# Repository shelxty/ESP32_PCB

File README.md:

# ESP32-C3 USB-C Devboard 

This is a custom 4-layer ESP32-C3 devboard built from scratch in KiCad, built around the ESP32-C3-WROOM-02. It's my second devboard (if a regulator can be counted as a devboard) with a full breakout of GPIOs and reset/boot buttons.

## Motivation 
This is my second-ever PCB; I built it to follow up on my first project. I've been interested in how ESP32s work so I thought this would be the best way to explore it! This would be an actual useful, purposeful tool that I'd be able to use in built projects as well. It also pushed me to learn new skills, like ESD protection and multi-layer board design (well, multi-layer as in 4 instead of 2). 

## How the Components Work 

| **Designator** | **Part** | **Purpose** | 
|----------------|----------|-------------|
| U3 | ESP32-C3-WROOM-02 | The brain of the board basically (it's a RISC-V microcontroller module that has integrated WiFi & bluetooth, along with an antenna) | 
| J1 | 16-pin USB-C receptacle | Power entry (it takes in 5V) | 
| J2, J3 | 8-pin headers on the left & right side, respectively | Breaks out the GPIO pins | 
| U1 | USBLC6-2SC6 | Dual line ESD protection IC that suppresses voltage spikes before they reach the microcontroller | 
| D1 | PESD5V0L1ULD | A TVS diode that protects the voltage line (5V) from any ESD/transient voltage spikes that enter from the USB receptacle | 
| R3 | 0Ω resistor | Basically a routing jumper so that I don't have to remove a trace | 
| U2 | AP2112K-3.3 | Fixed 3.3V, 600mA LDO regulator (it basically takes the 5V input and regulates it into a stable 3.3V rail) | 
| C1, C2 | 4.7uF capacitors | These are input and output capacitors built around the regulator that smooths the 5V input and the regulated 3.3V output | 
| C3, C4, C5 | 4.7uF capacitors | Other decoupline capacitors except these around the module's power pins, so the supply is stable even during WiFi bursts | 
| C9, C10 | 100nF capacitors | These are high-frequency decoupling capacitors that are placed close to the regulator's pins (they filter out noise) | 
| R5 | 10kΩ resistor | This is a pull-up resistor that supports the enable (EN) line | 
| R7, R8 | 10kΩ resistor | These are two other pull-up resistors except they support different GPIO lines | 
| R1, R2 | 5.1kΩ resistor | Resistors on the RESET and BOOT button lines, respectively | 
| SW1 | "RESET" Push Button | Basically just... resets the chip... yeah. | 
| SW2 | "BOOT" Push Button | Pulls IO9 (the strapping pin that selects boot mode, as opposed to UART download mode) low when it's pressed | 
| R9 | 10kΩ resistor | This one is another pull-up resistor but it specifically works on the IO9 boot/strapping line (so the chip should boot normally if the BOOT button isn't being pressed | 
| Y1 | Crystal | An external crystal that provides a precise clock reference | 

**Hardware**
- Tool: KiCad 10
- Board: 4-layer PCB (F.Cu / In1.Cu / In2.Cu / B.Cu)
- Microcontroller: ESP32-C3-WROOM-02 RISC-V, WiFi + Bluetooth
- Regulator: AP2112K-3.3, 600mA LDO
- USB protection: USBLC6-2SC6 (data line ESD) + PESD5V0L1ULD (VBUS TVS diode)
- Power input: USB-C (5V)
- GPIOs: 16 pins broken out across two 8-pin 2.54mm headers (J2, J3)
- Controls: Reset button (SW1), Boot button (SW2)

## PCB Design 

_Schematic of the board -- I made sure to add comments & my own personal text for beginners like me_

_PCB design_

_A 3D view of the actual thing_

## Bill of Materials 
| **Item** |	**Description** |	**Reference** |	**Qty** |	**MOQ** |	**Value** |	**Per Unit Price ($)** |	**Total Price ($)** |	**Footprint** |	**MPN** |	**URL** | 
|------|--------------|-----------|-----|-----|-------|--------------------|------------------|-----------|-----|-----|
| 4u7 Capacitor |	Unpolarized capacitor |	C1,C2,C3,C4,C5 |	5 |	10 |	4u7 |	0.0505 |	0.51 |	Capacitor_SMD:C_0805_2012Metric |	CL21A475KBQNNNE |	[Link](https://www.lcsc.com/product-detail/C98192.html?s_z=s_c_Ceramic%2520Capacitors&spm=wm.fly.bg.0.xh&lcsc_vid=QQVaAVJeTlJdUVBVE1hcBVFWEwcNBVxeQwAPA1YHFQMxVlNeRVFeXl1XRlNeXzsOAxUeFF5JWBYZEEoKFBINSQcJGk4NBhADEA4cHktTRk8GEwkK) |
| 100n Capacitor |	Unpolarized capacitor |	C6,C9,C10 |	3 |	10 |	100n |	0.0192 |	0.19 |	Capacitor_SMD:C_0201_0603Metric |	0805B104K500CT |	[Link](https://www.lcsc.com/product-detail/C83055.html?s_z=s_c_Ceramic%2520Capacitors&spm=wm.fly.bg.3.xh&lcsc_vid=QQVaAVJeTlJdUVBVE1hcBVFWEwcNBVxeQwAPA1YHFQMxVlNeRVFeXl1XRlNeXzsOAxUeFF5JWBYZEEoKFBINSQcJGk4NBhADEA4cHktTRk8GEwkK) |
| Capacitor |	Unpolarized capacitor |	C7,C8,R4 |	3 |	100 |	0n |	0.0052 |	0.52 |	Capacitor_SMD:C_0201_0603Metric |	TCC0805X7R501K500DT |	[Link](https://www.lcsc.com/product-detail/C5375938.html?spm=wm.fly.bg.3.xh&lcsc_vid=QQVaAVJeTlJdUVBVE1hcBVFWEwcNBVxeQwAPA1YHFQMxVlNeRVFfV1ZVTlNXVzsOAxUeFF5JWBYZEEoKFBINSQcJGk4NBhADEA4cHktXRlVcSQwSGg0%3D) |
| ESD Diode |	Low capacitance unidirectional ESD protection diode, 5V, SOD-882D |	D1 |	1 |	5 |	PESD5V0L1ULD |	0.0978 |	0.49 |	Diode_SMD:D_SOD-882D |	PESD5V0L1ULD,315 |	[Link](https://www.lcsc.com/product-detail/C552557.html?s_z=s_p_PESD5V0L1ULD%252C315&spm=wm.fly.bg.0.xh&lcsc_vid=QQVaAVJeTlJdUVBVE1hcBVFWEwcNBVxeQwAPA1YHFQMxVlNeRVFfV1dXRVBfUDsOAxUeFF5JWBYZEEoKFBINSQcJGk4dAgUUFAk%3D) | 
| USB-C Receptacle |	USB 2.0-only 16P Type-C Receptacle connector |	J1 |	1 |	5 |	USB_C_Receptacle_USB2.0_16P |	0.099 |	0.5 |	Connector_USB:USB_C_Receptacle_G-Switch_GT-USB-7010ASV |	USB-TYPE-C-016 |	[Link](https://www.lcsc.com/product-detail/C2927036.html?s_z=s_p_USB-TYPE-C-016&spm=wm.fly.bg.0.xh&lcsc_vid=QQVaAVJeTlJdUVBVE1hcBVFWEwcNBVxeQwAPA1YHFQMxVlNeRVFfV1BWRlFcVTsOAxUeFF5JWBYZEEoKFBINSQcJGk4dAgUUFAk%3D) |
| 1x08 Connector |	Generic connector, single row, 01x08 |	J2,J3 |	2 |	5 |	Conn_01x08_Pin |	0.558 |	2.79 |	Connector_PinHeader_2.54mm:PinHeader_1x08_P2.54mm_Vertical |	N/A |	[Link](https://www.aliexpress.us/item/3256807202794047.html?spm=a2g0o.detail.pcDetailTopMoreOtherSeller.3.5ee0z10vz10vCf&gps-id=pcDetailTopMoreOtherSeller&scm=1007.40050.354490.0&scm_id=1007.40050.354490.0&scm-url=1007.40050.354490.0&pvid=f02ca764-02d9-42b0-aa3a-38bc3d3eef3d&_t=gps-id%3ApcDetailTopMoreOtherSeller%2Cscm-url%3A1007.40050.354490.0%2Cpvid%3Af02ca764-02d9-42b0-aa3a-38bc3d3eef3d%2Ctpp_buckets%3A668%232846%238111%231996&pdp_ext_f=%7B%22order%22%3A%2215779%22%2C%22eval%22%3A%221%22%2C%22sceneId%22%3A%2230050%22%2C%22fromPage%22%3A%22recommend%22%7D&pdp_npi=6%40dis%21USD%211.66%211.64%21%21%211.66%211.64%21%402103128917820104935402726e66ac%2112000040551940967%21rec%21US%217756416958%21X%211%210%21n_tag%3A-29911%3Bd%3A882c3b75%3Bm03_new_user%3A-29895&utparam-url=scene%3ApcDetailTopMoreOtherSeller%7Cquery_from%3A%7Cx_object_id%3A1005007389108799%7C_p_origin_prod%3A) | 
| Resistor |	Resistor |	R1,R2 |	2 |	100 |	5k1 |	0.0022 |	0.22 |	Resistor_SMD:R_0805_2012Metric |	FRC0805J512TS |	[Link](https://www.lcsc.com/product-detail/C2930296.html?s_z=s_q_t_RESISTOR&spm=wm.fly.bg.1.xh___wm.ssy.tc.0.tz&lcsc_vid=QQVaAVJeTlJdUVBVE1hcBVFWEwcNBVxeQwAPA1YHFQMxVlNeRVFfV1JWT1RdVDsOAxUeFF5JWBYZEEoKFBINSQcJGk4NBhADEA4cHktRR1NADxALGw%3D%3D) |
| Resistor |	Resistor |	R3 |	1 |	100 |	0R |	0.003 |	0.3 |	Resistor_SMD:R_0805_2012Metric |	0805W8F0000T5E |	[Link](https://www.lcsc.com/product-detail/C17477.html?s_z=s_q_t_RESISTOR&spm=wm.fly.bg.0.xh___wm.ssy.tc.0.tz&lcsc_vid=QQVaAVJeTlJdUVBVE1hcBVFWEwcNBVxeQwAPA1YHFQMxVlNeRVFfV1JWT1RdVDsOAxUeFF5JWBYZEEoKFBINSQcJGk4NBhADEA4cHktRR1NADxALGw%3D%3D) |
| Resistor |	Resistor |	R5,R7,R8,R9 |	4 |	100 |	10k |	0.0031 |	0.31 |	Capacitor_SMD:C_0201_0603Metric |	FRC0805J103TS |	[Link](https://www.lcsc.com/product-detail/C2930231.html?s_z=s_q_t_RESISTOR&spm=wm.fly.bg.1.xh___wm.ssy.tc.0.tz&lcsc_vid=QQVaAVJeTlJdUVBVE1hcBVFWEwcNBVxeQwAPA1YHFQMxVlNeRVFfV1JWT1RdVDsOAxUeFF5JWBYZEEoKFBINSQcJGk4NBhADEA4cHktRR1NADxALGw%3D%3D) | 
| Resistor |	Resistor |	R4, R6 |	2 |	100 |	100R |	0.0031 |	0.31 |	Capacitor_SMD:C_0201_0603Metric |	FRC0805J101 TS |	[Link](https://www.lcsc.com/product-detail/C2907294.html?spm=wm.fly.bg.1.xh&lcsc_vid=QQVaAVJeTlJdUVBVE1hcBVFWEwcNBVxeQwAPA1YHFQMxVlNeRVFfV1xeTlRYUDsOAxUeFF5JWBYZEEoKFBINSQcJGk4NBhADEA4cHktXRlhXSQwSGg0%3D) | 
| Push Button |	Push button switch, generic, two pins |	SW1,SW2 |	2 |	10 |	SW_Push |	0.053 |	0.53 |	Button_Switch_SMD:SW_SPST_B3U-1000P |	TS-1088-AR02016 |	[Link](https://www.lcsc.com/product-detail/C720477.html?s_z=s_q_p_PUSH%2520BUTTON%2520SWITCH&spm=wm.ssy.bg.0.xh&lcsc_vid=QQVaAVJeTlJdUVBVE1hcBVFWEwcNBVxeQwAPA1YHFQMxVlNeRVFeVVRfQVlaXzsOAxUeFF5JWBYZEEoKFBINSQcJGk4NBhADEA4cHktfQVlADxALGw%3D%3D) | 
| ESD Diode |	Very low capacitance ESD protection diode, 2 data-line, SOT-23-6 |	U1 |	1 |	10 |	USBLC6-2SC6 |	0.041 |	0.41 |	Package_TO_SOT_SMD:SOT-23-6 |	USBLC6-2SC6 |	[Link](https://www.lcsc.com/product-detail/C2827654.html?s_z=s_p_USBLC6-2SC6&spm=wm.fly.bg.1.xh&lcsc_vid=QQVaAVJeTlJdUVBVE1hcBVFWEwcNBVxeQwAPA1YHFQMxVlNeRVFfVlRVQFJeVTsOAxUeFF5JWBYZEEoKFBINSQcJGk4dAgUUFAk%3D) | 
| Linear Regulator |	600mA low dropout linear regulator, with enable pin, 3.8V-6V input voltage range, 3.3V fixed positive output, SOT-23-5 |	U2 |	1 |	5 |	AP2112K-3.3 |	0.1093 |	0.55 |	Package_TO_SOT_SMD:SOT-23-5 |	AP2112K-3.3TRG1 |	[Link](https://www.lcsc.com/product-detail/C23380830.html?s_z=s_q_AP2112K-3.3&spm=wm.fly.bg.1.xh&lcsc_vid=QQVaAVJeTlJdUVBVE1hcBVFWEwcNBVxeQwAPA1YHFQMxVlNeRVFfVlReQ1BZXjsOAxUeFF5JWBYZEEoKFBINSQcJGk4dAgUUFAk%3D) | 
| ESP32-C3 |	802.11 b/g/n WiÂ­Fi and Bluetooth 5 module, ESP32Â­C3 SoC, RISCÂ­V microprocessor, On-board antenna |	U3 |	1 |	1 |	ESP32-C3-WROOM-02 |	3.33 |	3.33 |	RF_Module:ESP32-C3-WROOM-02 |	ESP32-C3-WROOM-02-H4 |	[Link](https://www.lcsc.com/product-detail/C2944070.html?s_z=n_q_ESP32-C3-WROOM-02&spm=wm.fly.bg.1.xh&lcsc_vid=QQVaAVJeTlJdUVBVE1hcBVFWEwcNBVxeQwAPA1YHFQMxVlNeRVFfVlVSQFZYXzsOAxUeFF5JWBYZEEoKFBINSQcJGk4eFQsCAgIaSgADAwAHC0slRVJdX1ReRFFADxALGw%3D%3D) | 
| Crystal |	Two pin crystal |	Y1 |	1 |	5 |	32.768kHz |	0.2461 |	1.23 |	Crystal:Crystal_SMD_3215-2Pin_3.2x1.5mm |	3608S-32.768DTTLLL-R35L |	[Link](https://www.lcsc.com/product-detail/C42392410.html?s_z=n_q_t_crystal&spm=wm.fly.bg.4.xh___wm.ssy.tc.0.tz&lcsc_vid=QQVaAVJeTlJdUVBVE1hcBVFWEwcNBVxeQwAPA1YHFQMxVlNeRVFfVlZUQ1VYUjsOAxUeFF5JWBYZEEoKFBINSQcJGk4eFQsCAgIaSgADAwAHC0slRVhaU1RRR08GEwkK) | 
| **Total** | | | 	**30** |	**566** | | |		**12.19**			|

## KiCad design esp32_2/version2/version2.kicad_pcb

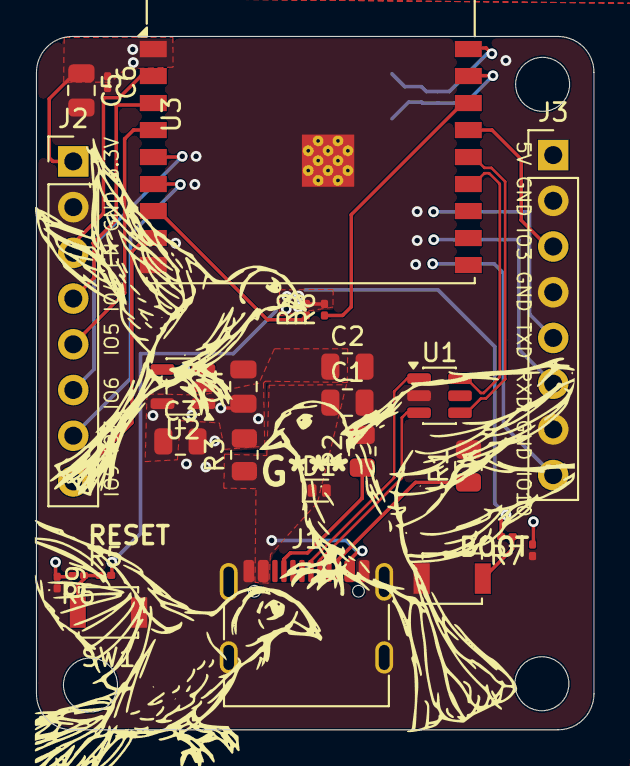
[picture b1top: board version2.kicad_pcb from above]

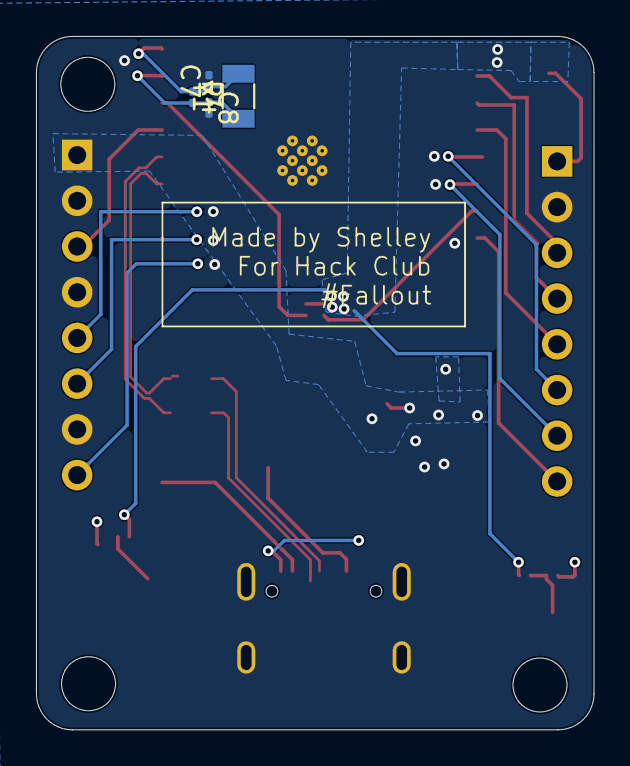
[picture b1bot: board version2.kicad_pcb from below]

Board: 4 copper layers, 31.0 x 38.5 mm, 29 parts (4 on the bottom side), 23 nets.

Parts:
C1, C2, C3, C4, C5: 4u7; C_0805_2012Metric
C6, C9, C10: 100n; C_0201_0603Metric
C7, C8: TBD; C_0201_0603Metric
D1: PESD5V0L1ULD; D_SOD-882D
J1: USB_C_Receptacle_USB2.0_16P; USB_C_Receptacle_G-Switch_GT-USB-7010ASV
J2, J3: Conn_01x08_Pin; PinHeader_1x08_P2.54mm_Vertical
R1, R2: 5k1; R_0805_2012Metric
R3: 0R; R_0805_2012Metric
R4: TBD; C_0201_0603Metric
R5, R7, R8, R9: 10k; C_0201_0603Metric
R6: 100R; C_0201_0603Metric
SW1, SW2: SW_Push; SW_SPST_B3U-1000P
U1: USBLC6-2SC6; SOT-23-6
U2: AP2112K-3.3; SOT-23-5
U3: ESP32-C3-WROOM-02
Y1: Crystal; Crystal_SMD_3215-2Pin_3.2x1.5mm

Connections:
+3V3: C5.1, C6.1, J2.1, R5.2, R7.2, R8.2, R9.2, U3.1 (3V3)
+5V: C2.1, C3.1, C4.1, J3.1, R3.2, U2.1 (VIN), U2.3 (EN), U2.5 (VOUT)
/D+: J1.A6 (D+), J1.B6 (D+), U1.3 (I/O2)
/D-: J1.A7 (D-), J1.B7 (D-), U1.1 (I/O1)
EN: C9.1, J2.3, R6.2, U3.2 (EN)
GND: C1.2, C2.2, C3.2, C4.2, C5.2, C6.2, C7.2, C8.2, C9.2, C10.2, D1.2 (A), J1.A1 (GND), J1.A12 (GND), J1.B1 (GND), J1.B12 (GND), J1.SH (SHIELD), J2.2, J3.2, J3.4, J3.7, R1.2, R2.2, SW1.1, SW2.1, U1.2 (GND), U2.2 (GND), U3.9 (GND), U3.19 (GND)
IO2: R8.1, U3.16 (IO2)
IO3: J3.3, U3.15 (IO3)
IO4: J2.4, U3.3 (IO4)
IO5: J2.5, U3.4 (IO5)
IO6: J2.6, U3.5 (IO6)
IO7: J2.7, U3.6 (IO7)
IO8: R9.1, U3.7 (IO8)
IO9: C10.1, J2.8, R7.1, SW2.2, U3.8 (IO9)
IO10: J3.8, U3.10 (IO10)
unnamed: J1.A5 (CC1), R2.1
unnamed: J1.B5 (CC2), R1.1
unnamed: R5.1, R6.1, SW1.2
unnamed: C7.1, R4.1, U3.18 (IO0), Y1.1
unnamed: C8.1, R4.2, U3.17 (IO1), Y1.2
USB_D+: U1.4 (I/O2), U3.14 (IO19)
USB_D-: U1.6 (I/O1), U3.13 (IO18)
VBUS: C1.1, D1.1 (K), J1.A4 (VBUS), J1.A9 (VBUS), J1.B4 (VBUS), J1.B9 (VBUS), R3.1

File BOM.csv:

Item,Description,Reference,Qty,MOQ,Value,Per Unit Price ($),Total Price ($),Footprint,MPN,URL,,,,,
4u7 Capacitor,Unpolarized capacitor,"C1,C2,C3,C4,C5",5,10,4u7,0.0505,0.51,Capacitor_SMD:C_0805_2012Metric,CL21A475KBQNNNE,https://www.lcsc.com/product-detail/C98192.html?s_z=s_c_Cera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,,,,,
100n Capacitor,Unpolarized capacitor,"C6,C9,C10",3,10,100n,0.0192,0.19,Capacitor_SMD:C_0201_0603Metric,0805B104K500CT,https://www.lcsc.com/product-detail/C83055.html?s_z=s_c_Cera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,,,,,
Capacitor,Unpolarized capacitor,"C7,C8,R4",3,100,0n,0.0052,0.52,Capacitor_SMD:C_0201_0603Metric,TCC0805X7R501K500DT,https://www.lcsc.com/product-detail/C5375938.html?spm=wm.fly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,,,,,
ESD Diode,"Low capacitance unidirectional ESD protection diode, 5V, SOD-882D",D1,1,5,PESD5V0L1ULD,0.0978,0.49,Diode_SMD:D_SOD-882D,"PESD5V0L1ULD,315",https://www.lcsc.com/product-detail/C552557.html?s_z=s_p_PES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,,,,,
USB-C Receptacle,USB 2.0-only 16P Type-C Receptacle connector,J1,1,5,USB_C_Receptacle_USB2.0_16P,0.099,0.5,Connector_USB:USB_C_Receptacle_G-Switch_GT-USB-7010ASV,USB-TYPE-C-016,https://www.lcsc.com/product-detail/C2927036.html?s_z=s_p_US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,,,,,
1x08 Connector,"Generic connector, single row, 01x08","J2,J3",2,5,Conn_01x08_Pin,0.558,2.79,Connector_PinHeader_2.54mm:PinHeader_1x08_P2.54mm_Vertical,N/A,https://www.aliexpress.us/item/3256807202794047.html?spm=a2g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,,,,,
Resistor,Resistor,"R1,R2",2,100,5k1,0.0022,0.22,Resistor_SMD:R_0805_2012Metric,FRC0805J512TS,https://www.lcsc.com/product-detail/C2930296.html?s_z=s_q_t_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,,,,,
Resistor,Resistor,R3,1,100,0R,0.003,0.3,Resistor_SMD:R_0805_2012Metric,0805W8F0000T5E,https://www.lcsc.com/product-detail/C17477.html?s_z=s_q_t_RE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,,,,,
Resistor,Resistor,"R5,R7,R8,R9",4,100,10k,0.0031,0.31,Capacitor_SMD:C_0201_0603Metric,FRC0805J103TS,https://www.lcsc.com/product-detail/C2930231.html?s_z=s_q_t_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,,,,,
Resistor,Resistor,"R4, R6",2,100,100R,0.0031,0.31,Capacitor_SMD:C_0201_0603Metric,FRC0805J101 TS,https://www.lcsc.com/product-detail/C2907294.html?spm=wm.fly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,,,,,
Push Button,"Push button switch, generic, two pins","SW1,SW2",2,10,SW_Push,0.053,0.53,Button_Switch_SMD:SW_SPST_B3U-1000P,TS-1088-AR02016,https://www.lcsc.com/product-detail/C720477.html?s_z=s_q_p_P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,,,,,
ESD Diode,"Very low capacitance ESD protection diode, 2 data-line, SOT-23-6",U1,1,10,USBLC6-2SC6,0.041,0.41,Package_TO_SOT_SMD:SOT-23-6,USBLC6-2SC6,https://www.lcsc.com/product-detail/C2827654.html?s_z=s_p_US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,,,,,
Linear Regulator,"600mA low dropout linear regulator, with enable pin, 3.8V-6V input voltage range, 3.3V fixed positive output, SOT-23-5",U2,1,5,AP2112K-3.3,0.1093,0.55,Package_TO_SOT_SMD:SOT-23-5,AP2112K-3.3TRG1,https://www.lcsc.com/product-detail/C23380830.html?s_z=s_q_A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,,,,,
ESP32-C3,"802.11 b/g/n Wi­Fi and Bluetooth 5 module, ESP32­C3 SoC, RISC­V microprocessor, On-board antenna",U3,1,1,ESP32-C3-WROOM-02,3.33,3.33,RF_Module:ESP32-C3-WROOM-02,ESP32-C3-WROOM-02-H4,https://www.lcsc.com/product-detail/C2944070.html?s_z=n_q_ES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,,,,,
Crystal,Two pin crystal,Y1,1,5,32.768kHz,0.2461,1.23,Crystal:Crystal_SMD_3215-2Pin_3.2x1.5mm,3608S-32.768DTTLLL-R35L,https://www.lcsc.com/product-detail/C42392410.html?s_z=n_q_t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,,,,,
Total,,,30,566,,,12.19,,,,,,,,
,,,,,,,,,,,,,,,
,,,,,,,,,,,,,,,
,,,,,,,,,,,,,,,

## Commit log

2026-05-12 test1
2026-05-12 aaaaaaaaaaaaaaaa
2026-05-14 wiring, connections between cp2104 and the usb c receptacle and stuffs
2026-06-17 finished schematic v2
2026-06-19 added copper fill vbus
2026-06-20 added some more routing and copper filling for 5v and 3v3
2026-06-20 fixed up some other basic routing issues i hate this
2026-06-20 more routing more vias more visas (not)
2026-06-20 i feel stupid because the reason everything was breaking because i added an extra gnd pin in my schematic when i wasn't supposed to
2026-06-20 finished routing
2026-06-20 finished routing and finished pcb design!
2026-06-20 oops had to fix one thing
2026-06-21 Delete esp32pcb directory
    This was my version 1 and therefore doesn't need to be here.
2026-06-21 working on readme
2026-06-21 BOM
    bom
2026-06-21 renamed bom to bom
2026-06-21 added zine
    aaaa
2026-06-21 zine pdf
2026-06-21 fixed up readme
2026-06-22 edited mounting holes
2026-06-22 oops some formatting stuff
2026-06-24 Rename version2.kicad_pcb to version2.kicad_pcb
